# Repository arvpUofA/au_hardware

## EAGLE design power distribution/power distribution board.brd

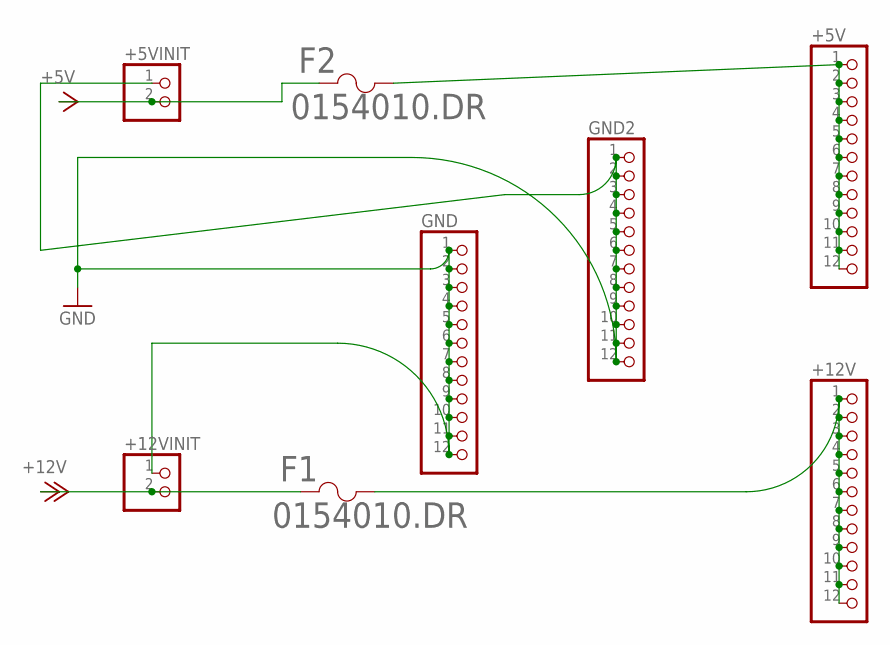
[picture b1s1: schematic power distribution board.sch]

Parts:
+5V, +12V: TERM_BLOCK_12
+5VINIT, +12VINIT: TERM_BLOCK_2TERM_BLOCK_2; 1X02
F1, F2: 0154010.DR; 0154SERIES
GND, GND2: TERM_BLOCK_12

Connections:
+5V: +5VINIT.2, F2.1
+5VDIST: +5V.1, +5V.2, +5V.3, +5V.4, +5V.5, +5V.6, +5V.7, +5V.8, +5V.9, +5V.10, +5V.11, +5V.12, F2.2
+12V: +12VINIT.2, F1.1
+12VDIST: +12V.1, +12V.2, +12V.3, +12V.4, +12V.5, +12V.6, +12V.7, +12V.8, +12V.9, +12V.10, +12V.11, +12V.12, F1.2
GND: +5VINIT.1, +12VINIT.1, GND.1, GND.2, GND.3, GND.4, GND.5, GND.6, GND.7, GND.8, GND.9, GND.10, GND.11, GND.12, GND2.1, GND2.2, GND2.3, GND2.4, GND2.5, GND2.6, GND2.7, GND2.8, GND2.9, GND2.10, GND2.11, GND2.12

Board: 2 copper layers, 8 parts (0 on the bottom side), 5 nets, no tracks yet.

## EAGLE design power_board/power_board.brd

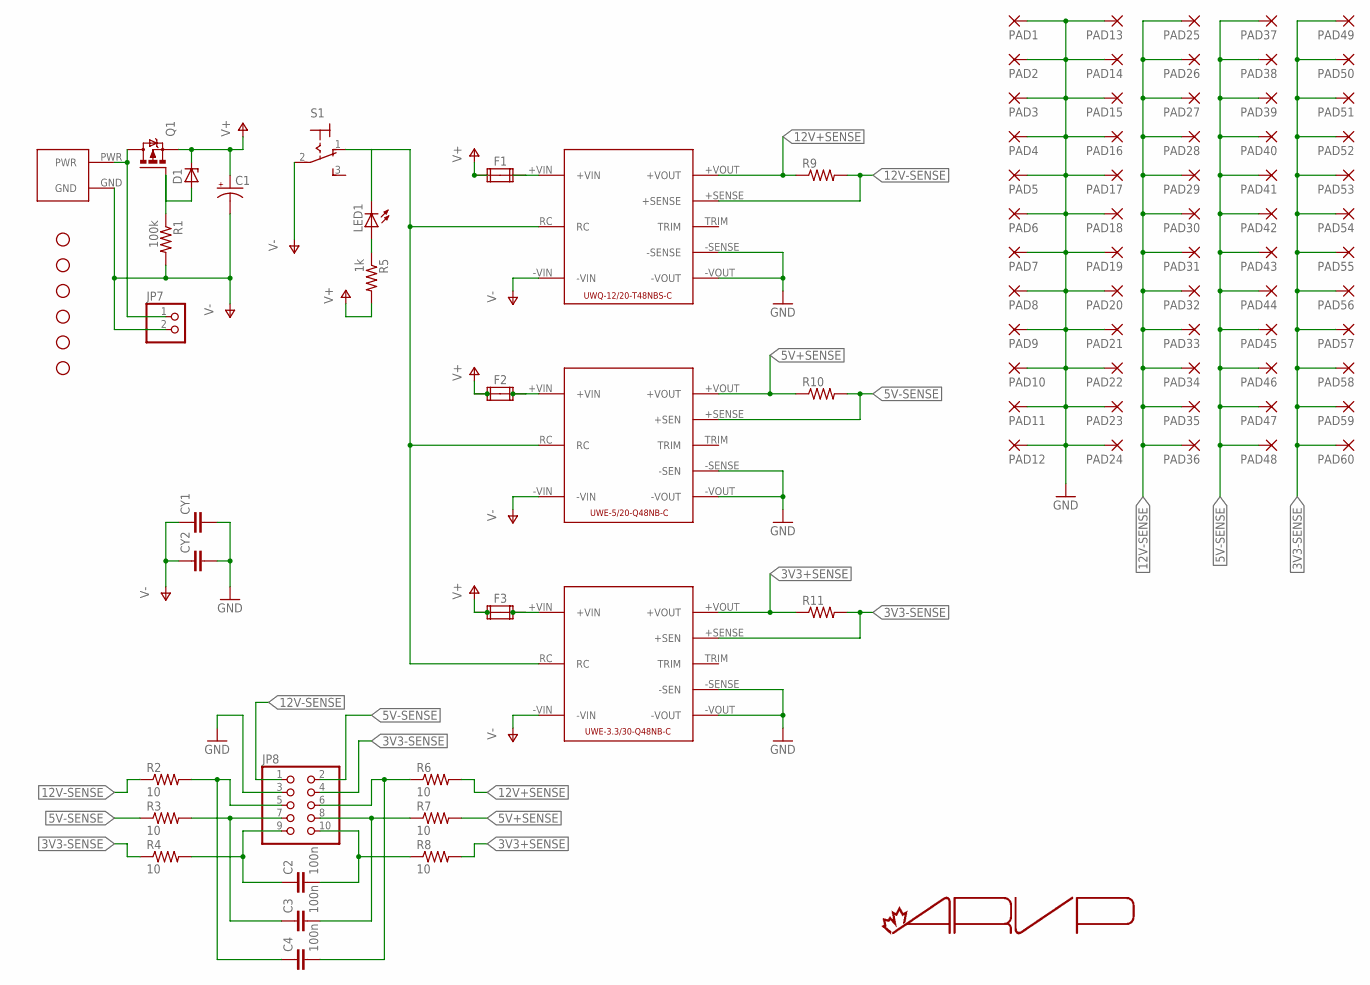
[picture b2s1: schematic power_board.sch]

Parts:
C1: CPOL-USE5-10.5; E5-10,5
C2, C3, C4: 100n; C025-024X044
CY1, CY2: CYYC7B5; YC7B5
D1: ZENER-DIODEDO35Z10; DO35Z10
F1, F2, F3: FUSE2P; FUSE1
JP1, JP2, JP3, JP4, JP5, JP6: STAND-OFF
JP7: PINHD-1X2; 1X02
JP8: PINHD-2X5; 2X05
LED1: LED3MM
P$1: AND_PWR
PAD1, PAD2, PAD3, PAD4, PAD5, PAD6, PAD7, PAD8, PAD9, PAD10, PAD11, PAD12, PAD13, PAD14, PAD15, PAD16, PAD17, PAD18, PAD19, PAD20, PAD21, PAD22, PAD23, PAD24, PAD25, PAD26, PAD27, PAD28, PAD29, PAD30, PAD31, PAD32, PAD33, PAD34, PAD35, PAD36, PAD37, PAD38, PAD39, PAD40, PAD41, PAD42, PAD43, PAD44, PAD45, PAD46, PAD47, PAD48, PAD49, PAD50, PAD51, PAD52, PAD53, PAD54, PAD55, PAD56, PAD57, PAD58, PAD59, PAD60: 2,15/1,0
Q1: IPP80P03P4L04AKSA1; TO220BV
R1: 100k; 0204/7
R2, R3, R4, R6, R7, R8: 10; 0204/5
R5: 1k; 0204/7
R9, R10, R11: R-US_0617/22; 0617/22
S1: M9040P
U1: UWQ-12/20-T48NBS-C; UWQ-12/20-T48
U2: UWE-5/20-Q48NB-C; UWE-100-120W
U3: UWE-3.3/30-Q48NB-C; UWE-100-120W

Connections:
3V3+SENSE: R8.2, R11.1, U3.+VOUT
3V3-SENSE: JP8.4, PAD49.1, PAD50.1, PAD51.1, PAD52.1, PAD53.1, PAD54.1, PAD55.1, PAD56.1, PAD57.1, PAD58.1, PAD59.1, PAD60.1, R4.1, R11.2, U3.+SENSE (+SEN)
5V+SENSE: R7.2, R10.1, U2.+VOUT
5V-SENSE: JP8.2, PAD37.1, PAD38.1, PAD39.1, PAD40.1, PAD41.1, PAD42.1, PAD43.1, PAD44.1, PAD45.1, PAD46.1, PAD47.1, PAD48.1, R3.1, R10.2, U2.+SENSE (+SEN)
12V+SENSE: R6.2, R9.1, U1.+VOUT
12V-SENSE: JP8.1, PAD25.1, PAD26.1, PAD27.1, PAD28.1, PAD29.1, PAD30.1, PAD31.1, PAD32.1, PAD33.1, PAD34.1, PAD35.1, PAD36.1, R2.1, R9.2, U1.+SENSE
GND: CY1.2, CY2.2, JP8.3, PAD1.1, PAD2.1, PAD3.1, PAD4.1, PAD5.1, PAD6.1, PAD7.1, PAD8.1, PAD9.1, PAD10.1, PAD11.1, PAD12.1, PAD13.1, PAD14.1, PAD15.1, PAD16.1, PAD17.1, PAD18.1, PAD19.1, PAD20.1, PAD21.1, PAD22.1, PAD23.1, PAD24.1, U1.-SENSE, U1.-VOUT, U2.-SENSE (-SEN), U2.-VOUT, U3.-SENSE (-SEN), U3.-VOUT
J3: C4.1, JP8.5, R2.2
J4: C4.2, JP8.6, R6.1
J5: C3.1, JP8.7, R3.2
J6: C3.2, JP8.8, R7.1
J7: C2.1, JP8.9, R4.2
J8: C2.2, JP8.10, R8.1
unnamed: LED1.A, R5.1
unnamed: D1.A, Q1.G, R1.1
unnamed: F1.2A, F1.2B, U1.+VIN
unnamed: F2.2A, F2.2B, U2.+VIN
unnamed: F3.2A, F3.2B, U3.+VIN
ON/OFF: LED1.K (C), S1.1 (O), U1.RC, U2.RC, U3.RC
V+: C1.+, D1.C, F1.1A, F1.1B, F2.1A, F2.1B, F3.1A, F3.1B, Q1.S, R5.2
V-: C1.-, CY1.1, CY2.1, JP7.2, P$1.GND, R1.2, S1.2, U1.-VIN, U2.-VIN, U3.-VIN
VBAT+: JP7.1, P$1.PWR, Q1.D

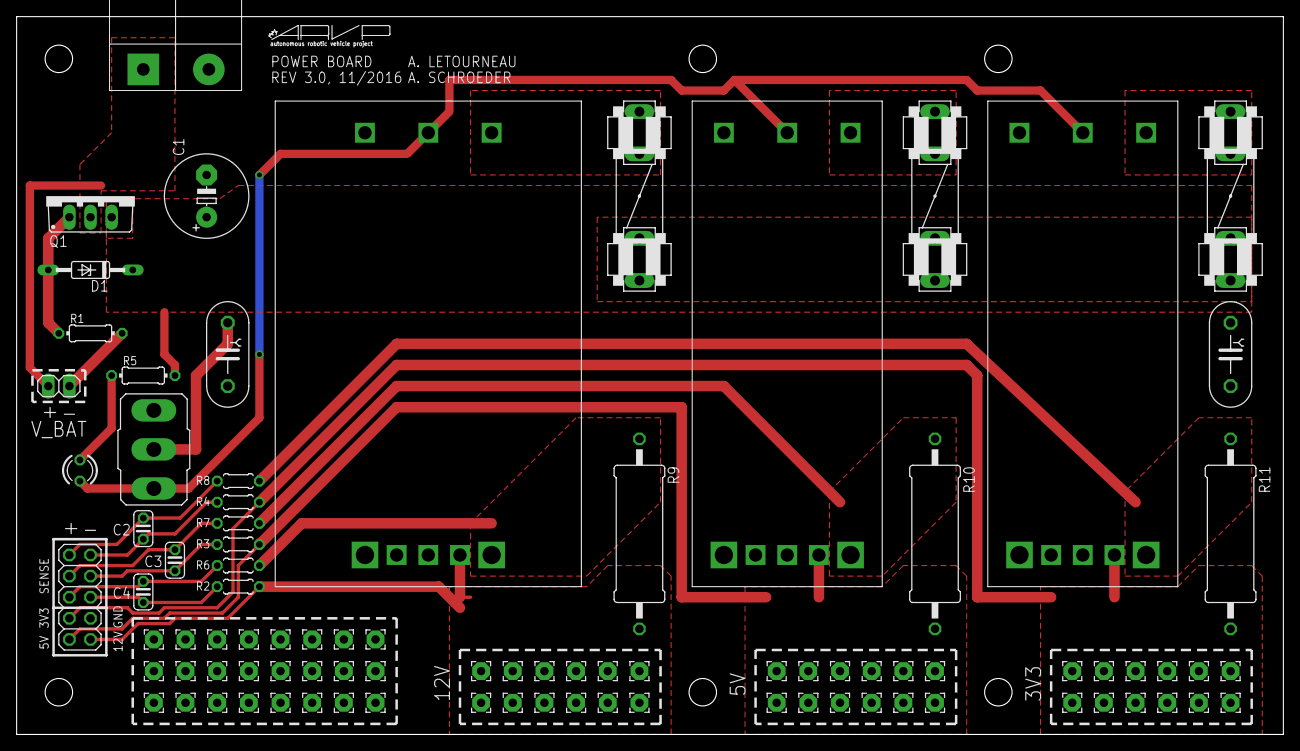
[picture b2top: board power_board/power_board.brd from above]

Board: 2 copper layers, 152.4 x 86.4 mm, 99 parts (0 on the bottom side), 22 nets.

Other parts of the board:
U$1: DINA5_L
U$2: DOCFIELD
U$3: ARVP

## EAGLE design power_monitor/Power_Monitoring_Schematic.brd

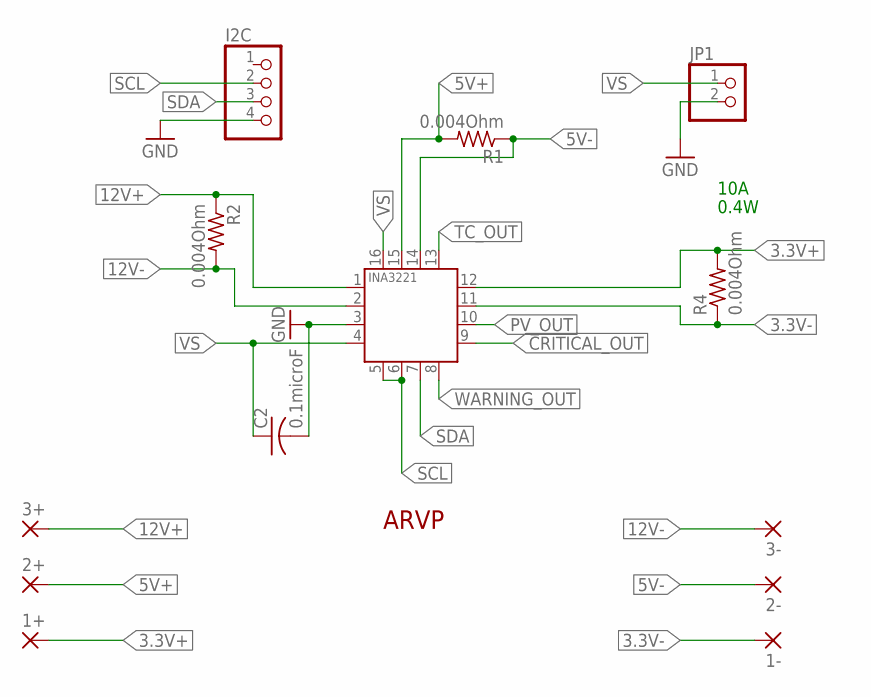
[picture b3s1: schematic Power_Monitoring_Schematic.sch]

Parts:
1+, 1-, 2+, 2-, 3+, 3-: 3,81/1,5A; 3,81/1,5
ARVP1: ARVP_LOGO; ARVP
C2: 0.1microF; C2012
I2C: PINHD-1X4; 1X04
JP1: PINHD-1X2; 1X02
R1, R2, R4: 0.004Ohm; R1206
U1: INA3221.; HVQFN16_4X4

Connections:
3.3V+: 1+.1, R4.2, U1.12 (IN+1)
3.3V-: 1-.1, R4.1, U1.11 (IN-1)
5V+: 2+.1, R1.2, U1.15 (IN+2)
5V-: 2-.1, R1.1, U1.14 (IN-2)
12V+: 3+.1, R2.1, U1.1 (IN-3)
12V-: 3-.1, R2.2, U1.2 (IN+3)
CRITICAL_OUT: U1.9 (CRITICAL)
GND: C2.2, I2C.4, JP1.2, U1.3 (GND)
PV_OUT: U1.10 (PV)
SCL: I2C.2, U1.5 (A0), U1.6 (SCL)
SDA: I2C.3, U1.7 (SDA)
TC_OUT: U1.13 (TC)
VS: C2.1, JP1.1, U1.4 (VS), U1.16 (VPU)
WARNING_OUT: U1.8 (WARNING)

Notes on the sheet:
0.4W
10A

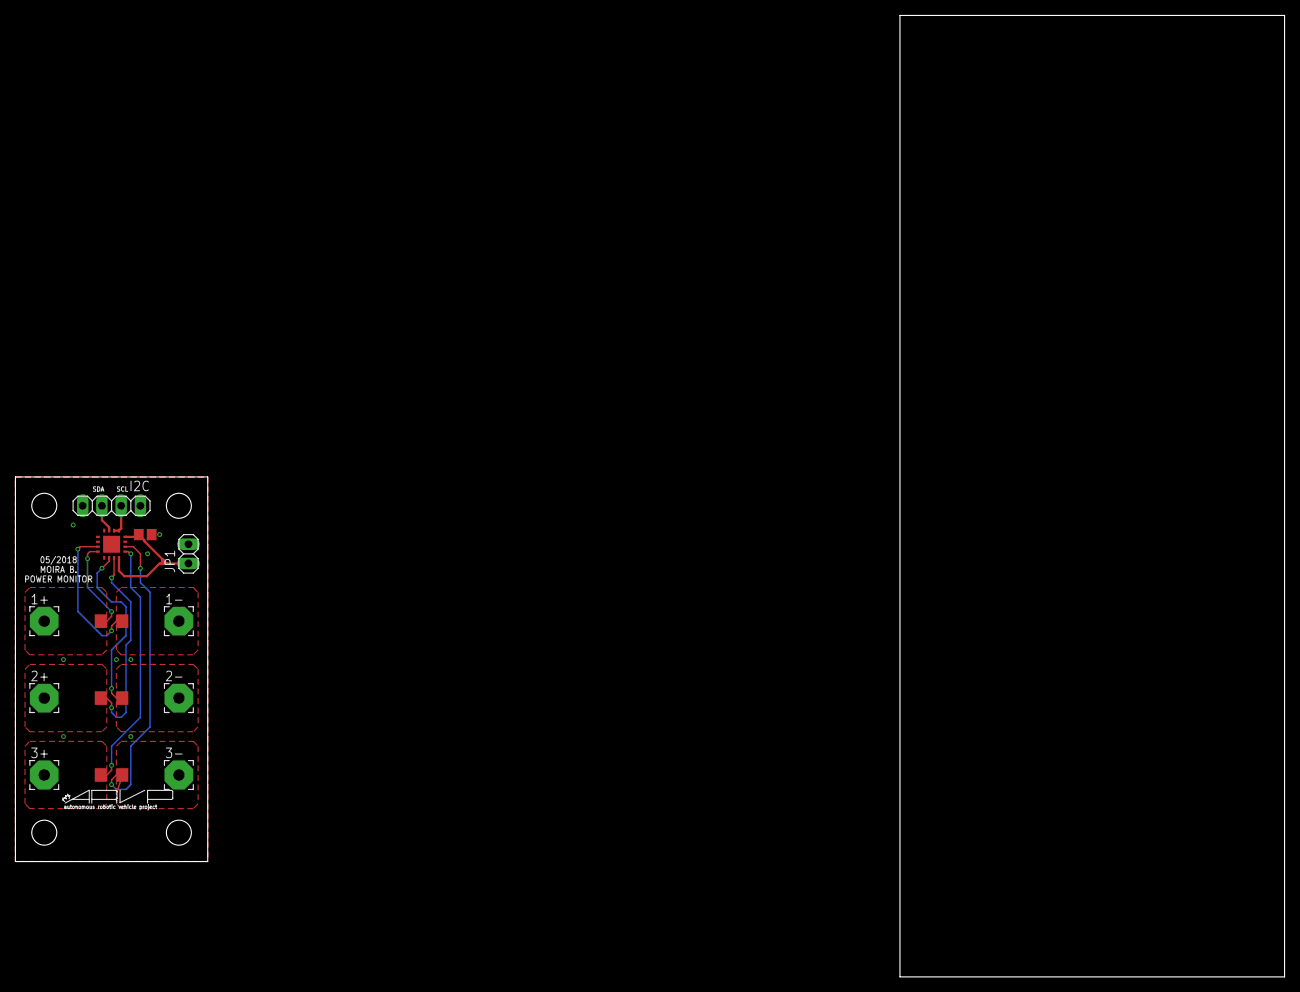
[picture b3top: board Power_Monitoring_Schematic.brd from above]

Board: 2 copper layers, 25.4 x 50.8 mm, 18 parts (0 on the bottom side), 10 nets.

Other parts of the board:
U$1, U$2, U$3, U$4: STAND-OFF

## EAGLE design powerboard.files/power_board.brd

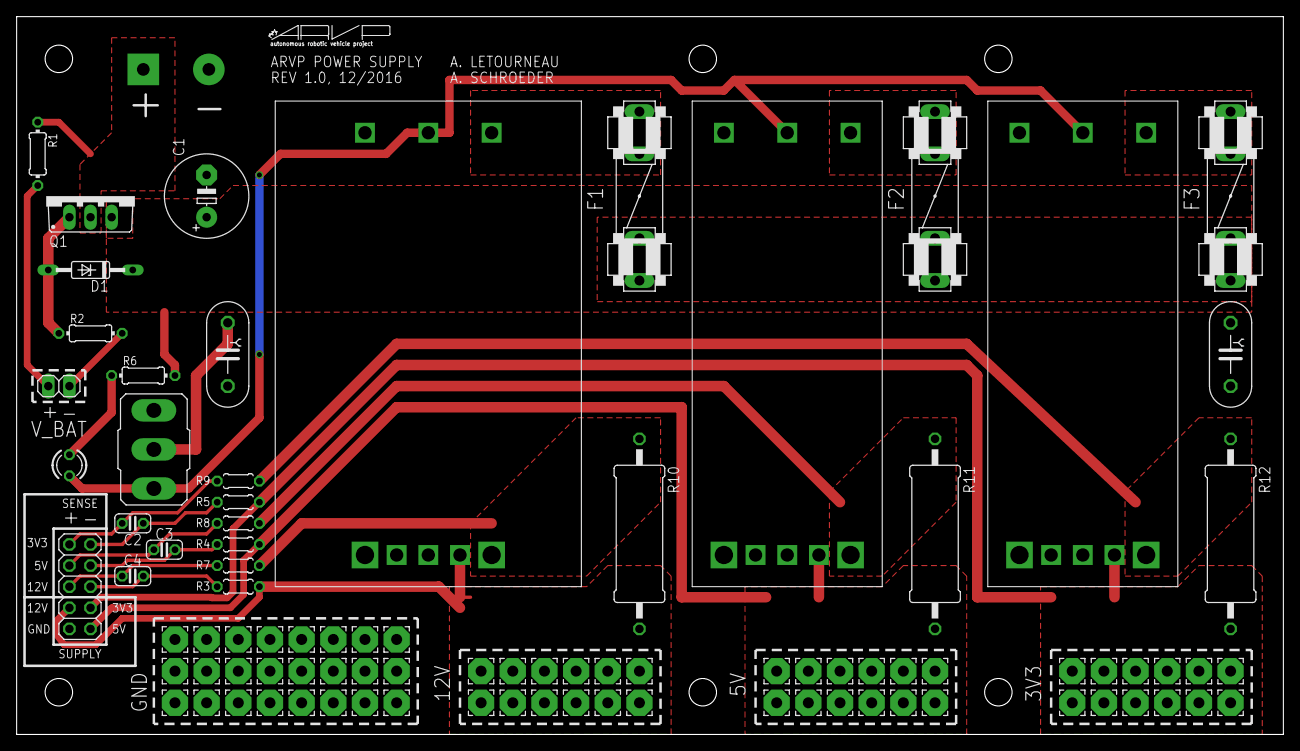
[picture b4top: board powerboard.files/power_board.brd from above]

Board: 2 copper layers, 152.4 x 86.4 mm, 100 parts (0 on the bottom side), 23 nets.

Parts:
C1: E5-10,5
C2, C3, C4: 100n; C025-024X044
CY1, CY2: YC7B5
D1: DO35Z10
F1, F2, F3: FUSE1
JP1, JP2, JP3, JP4, JP5, JP6: STAND-OFF
JP7: 1X02
JP8: 2X05
LED1: LED3MM
P$1: AND_PWR
PAD1, PAD2, PAD3, PAD4, PAD5, PAD6, PAD7, PAD8, PAD9, PAD10, PAD11, PAD12, PAD13, PAD14, PAD15, PAD16, PAD17, PAD18, PAD19, PAD20, PAD21, PAD22, PAD23, PAD24, PAD25, PAD26, PAD27, PAD28, PAD29, PAD30, PAD31, PAD32, PAD33, PAD34, PAD35, PAD36, PAD37, PAD38, PAD39, PAD40, PAD41, PAD42, PAD43, PAD44, PAD45, PAD46, PAD47, PAD48, PAD49, PAD50, PAD51, PAD52, PAD53, PAD54, PAD55, PAD56, PAD57, PAD58, PAD59, PAD60: WIREPAD3,17/1,3; 3,17/1,3
Q1: IPP80P03P4L04AKSA1; TO220BV
R1, R6: 1k; 0204/7
R2: 100k; 0204/7
R3, R4, R5, R7, R8, R9: 10; 0204/5
R10, R11, R12: 0.004; 0617/22
S1: M9040P
U1: UWQ-12/20-T48NBS-C; UWQ-12/20-T48
U2: UWE-5/20-Q48NB-C; UWE-100-120W
U3: UWE-3.3/30-Q48NB-C; UWE-100-120W
U$1: DINA5_L
U$2: DOCFIELD
U$3: ARVP

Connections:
3V3+SENSE: R9.2, R12.1, U3.+VOUT
3V3-SENSE: JP8.3, PAD49.1, PAD50.1, PAD51.1, PAD52.1, PAD53.1, PAD54.1, PAD55.1, PAD56.1, PAD57.1, PAD58.1, PAD59.1, PAD60.1, R5.1, R12.2, U3.+SENSE
5V+SENSE: R8.2, R11.1, U2.+VOUT
5V-SENSE: JP8.1, PAD37.1, PAD38.1, PAD39.1, PAD40.1, PAD41.1, PAD42.1, PAD43.1, PAD44.1, PAD45.1, PAD46.1, PAD47.1, PAD48.1, R4.1, R11.2, U2.+SENSE
12V+SENSE: R7.2, R10.1, U1.+VOUT
12V-SENSE: JP8.4, PAD25.1, PAD26.1, PAD27.1, PAD28.1, PAD29.1, PAD30.1, PAD31.1, PAD32.1, PAD33.1, PAD34.1, PAD35.1, PAD36.1, R3.1, R10.2, U1.+SENSE
GND: CY1.2, CY2.2, JP8.2, PAD1.1, PAD2.1, PAD3.1, PAD4.1, PAD5.1, PAD6.1, PAD7.1, PAD8.1, PAD9.1, PAD10.1, PAD11.1, PAD12.1, PAD13.1, PAD14.1, PAD15.1, PAD16.1, PAD17.1, PAD18.1, PAD19.1, PAD20.1, PAD21.1, PAD22.1, PAD23.1, PAD24.1, U1.-SENSE, U1.-VOUT, U2.-SENSE, U2.-VOUT, U3.-SENSE, U3.-VOUT
J3: C4.1, JP8.5, R3.2
J4: C4.2, JP8.6, R7.1
J5: C3.1, JP8.7, R4.2
J6: C3.2, JP8.8, R8.1
J7: C2.1, JP8.9, R5.2
J8: C2.2, JP8.10, R9.1
unnamed: LED1.A, R6.1
unnamed: JP7.1, R1.2
unnamed: D1.A, Q1.G, R2.1
unnamed: F1.2A, F1.2B, U1.+VIN
unnamed: F2.2A, F2.2B, U2.+VIN
unnamed: F3.2A, F3.2B, U3.+VIN
ON/OFF: LED1.K, S1.1, U1.RC, U2.RC, U3.RC
V+: C1.+, D1.C, F1.1A, F1.1B, F2.1A, F2.1B, F3.1A, F3.1B, Q1.S, R6.2
V-: C1.-, CY1.1, CY2.1, JP7.2, P$1.GND, R2.2, S1.2, U1.-VIN, U2.-VIN, U3.-VIN
VBAT+: P$1.PWR, Q1.D, R1.1

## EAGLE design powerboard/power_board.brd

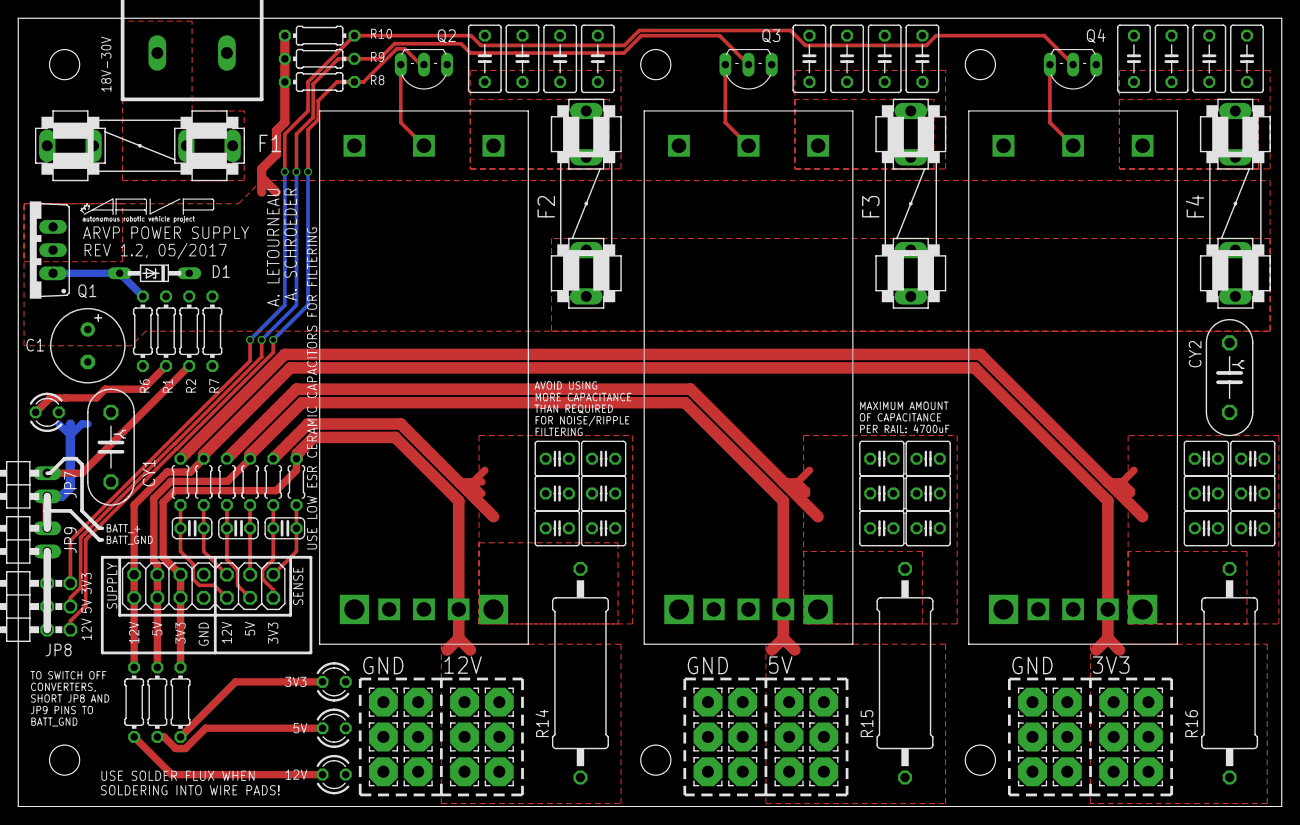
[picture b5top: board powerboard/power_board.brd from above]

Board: 2 copper layers, 138.4 x 86.4 mm, 121 parts (0 on the bottom side), 33 nets.

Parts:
C1: 100u; E3,5-8
C2, C3, C4: 100n; C025-024X044
C5, C6, C7, C8, C9, C10, C11, C12, C13, C14, C15, C16: C050-035X075
C17, C18, C19, C20, C21, C22, C23, C24, C25, C26, C27, C28, C29, C30, C31, C32, C33, C34: C025-040X050
CY1, CY2: YC7B5
D1: BZV10; DO34Z7
F1, F2, F3, F4: FUSE1
JP1, JP2, JP3, JP4, JP5, JP6: STAND-OFF
JP7, JP9: 1X02/90
JP8: 2X03/90
JP10: 2X07
LED1, LED2, LED3, LED4: LED3MM
PAD1, PAD2, PAD3, PAD4, PAD5, PAD6, PAD7, PAD8, PAD9, PAD10, PAD11, PAD12, PAD13, PAD14, PAD15, PAD16, PAD17, PAD18, PAD19, PAD20, PAD21, PAD22, PAD23, PAD24, PAD25, PAD26, PAD27, PAD28, PAD29, PAD30, PAD31, PAD32, PAD33, PAD34, PAD35, PAD36: WIREPAD3,17/1,3; 3,17/1,3
Q1: IPP80P03P4L04AKSA1; TO220BV
Q2, Q3, Q4: 2N4401TFR; TO92-EBC
R1, R17, R18, R19: 36k; 0204/7
R2, R7: 4.7k; 0204/7
R3, R4, R5, R11, R12, R13: 10; 0204/5
R6: 2k; 0204/7
R8, R9, R10: 10k; 0204/7
R14, R15, R16: 0.004; 0617/22
T1: 2_POS_TERMINAL; PHOENIX_CONTACT_MKDS_5/2-7.62
U1: UWE-5/20-Q48NB-C; UWE-100-120W
U2: UWE-3.3/30-Q48NB-C; UWE-100-120W
U4: UWE-12/10-Q48NB-C; UWE-100-120W
U$1: FRAME_A_L
U$2: DOCFIELD
U$3: ARVP

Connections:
3V3+SENSE: C21.1, C22.1, C27.1, C28.1, C33.1, C34.1, R3.1, R16.1, U2.+VOUT
3V3-SENSE: JP10.1, JP10.2, PAD31.1, PAD32.1, PAD33.1, PAD34.1, PAD35.1, PAD36.1, R11.2, R16.2, R19.2, U2.+SENSE
5V+SENSE: C19.1, C20.1, C25.1, C26.1, C31.1, C32.1, R4.1, R15.1, U1.+VOUT
5V-SENSE: JP10.3, JP10.4, PAD25.1, PAD26.1, PAD27.1, PAD28.1, PAD29.1, PAD30.1, R12.2, R15.2, R18.2, U1.+SENSE
12V+SENSE: C17.1, C18.1, C23.1, C24.1, C29.1, C30.1, R5.1, R14.1, U4.+VOUT
12V-SENSE: JP10.5, JP10.6, PAD19.1, PAD20.1, PAD21.1, PAD22.1, PAD23.1, PAD24.1, R13.2, R14.2, R17.2, U4.+SENSE
ENABLE_3V3: Q4.C, U2.RC
ENABLE_5V: Q3.C, U1.RC
ENABLE_12V: Q2.C, U4.RC
GND: C17.2, C18.2, C19.2, C20.2, C21.2, C22.2, C23.2, C24.2, C25.2, C26.2, C27.2, C28.2, C29.2, C30.2, C31.2, C32.2, C33.2, C34.2, CY1.2, CY2.2, JP10.7, JP10.8, LED2.K, LED3.K, LED4.K, PAD1.1, PAD2.1, PAD3.1, PAD4.1, PAD5.1, PAD6.1, PAD7.1, PAD8.1, PAD9.1, PAD10.1, PAD11.1, PAD12.1, PAD13.1, PAD14.1, PAD15.1, PAD16.1, PAD17.1, PAD18.1, U1.-SENSE, U1.-VOUT, U2.-SENSE, U2.-VOUT, U4.-SENSE, U4.-VOUT
J3: C4.1, JP10.9, R3.2
J4: C4.2, JP10.10, R11.1
J5: C3.1, JP10.11, R4.2
J6: C3.2, JP10.12, R12.1
J7: C2.1, JP10.13, R5.2
J8: C2.2, JP10.14, R13.1
unnamed: LED1.A, R1.1
unnamed: JP7.2, R2.2
unnamed: F1.1A, F1.1B, T1.P$1
unnamed: D1.A, Q1.G, R6.1
unnamed: C5.1, C6.1, C11.1, C12.1, F2.2A, F2.2B, U4.+VIN
unnamed: C7.1, C8.1, C13.1, C14.1, F3.2A, F3.2B, U1.+VIN
unnamed: JP8.2, JP8.4, JP8.6, JP9.1
unnamed: LED2.A, R17.1
unnamed: LED3.A, R18.1
unnamed: LED4.A, R19.1
unnamed: C9.1, C10.1, C15.1, C16.1, F4.2A, F4.2B, U2.+VIN
ON/OFF_1: JP8.1, Q2.B, R8.2
ON/OFF_2: JP8.3, Q3.B, R9.2
ON/OFF_3: JP8.5, Q4.B, R10.2
V+: C1.+, D1.C, F2.1A, F2.1B, F3.1A, F3.1B, F4.1A, F4.1B, Q1.S, R1.2, R2.1, R7.1, R8.1, R9.1, R10.1
V-: C1.-, C5.2, C6.2, C7.2, C8.2, C9.2, C10.2, C11.2, C12.2, C13.2, C14.2, C15.2, C16.2, CY1.1, CY2.1, JP7.1, JP9.2, LED1.K, Q2.E, Q3.E, Q4.E, R6.2, R7.2, T1.P$2, U1.-VIN, U2.-VIN, U4.-VIN
VBAT+: F1.2A, F1.2B, Q1.D

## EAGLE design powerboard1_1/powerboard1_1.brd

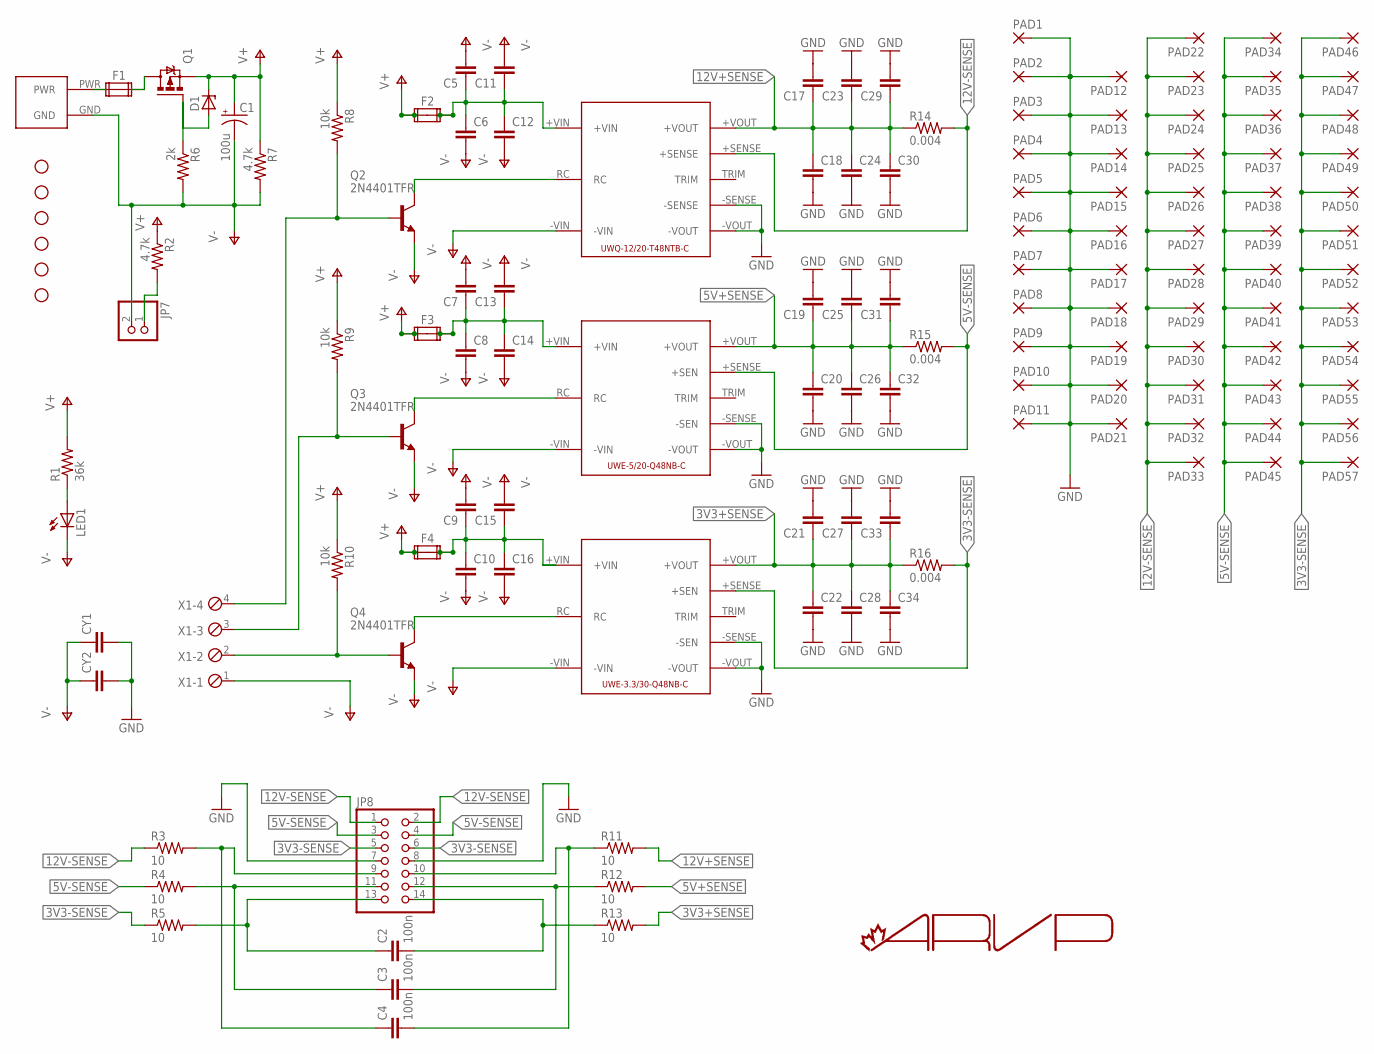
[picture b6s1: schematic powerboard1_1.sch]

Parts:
C1: 100u; E3,5-8
C2, C3, C4: 100n; C025-024X044
C5, C6, C7, C8, C9, C10, C11, C12, C13, C14, C15, C16: C-EU050-035X075; C050-035X075
C17, C18, C19, C20, C21, C22, C23, C24, C25, C26, C27, C28, C29, C30, C31, C32, C33, C34: C-EU025-040X050; C025-040X050
CY1, CY2: CYYC7B5; YC7B5
D1: BZV10; DO34Z7
F1, F2, F3, F4: FUSE2P; FUSE1
JP1, JP2, JP3, JP4, JP5, JP6: STAND-OFF
JP7: PINHD-1X2; 1X02
JP8: PINHD-2X7; 2X07
LED1: LED3MM
P$1: AND_PWR
PAD1, PAD2, PAD3, PAD4, PAD5, PAD6, PAD7, PAD8, PAD9, PAD10, PAD11, PAD12, PAD13, PAD14, PAD15, PAD16, PAD17, PAD18, PAD19, PAD20, PAD21, PAD22, PAD23, PAD24, PAD25, PAD26, PAD27, PAD28, PAD29, PAD30, PAD31, PAD32, PAD33, PAD34, PAD35, PAD36, PAD37, PAD38, PAD39, PAD40, PAD41, PAD42, PAD43, PAD44, PAD45, PAD46, PAD47, PAD48, PAD49, PAD50, PAD51, PAD52, PAD53, PAD54, PAD55, PAD56, PAD57: WIREPAD3,17/1,3; 3,17/1,3
Q1: IPP80P03P4L04AKSA1; TO220BV
Q2, Q3, Q4: 2N4401TFR; TO92-EBC
R1: 36k; 0204/7
R2, R7: 4.7k; 0204/7
R3, R4, R5, R11, R12, R13: 10; 0204/5
R6: 2k; 0204/7
R8, R9, R10: 10k; 0204/7
R14, R15, R16: 0.004; 0617/22
U1: UWQ-12/20-T48NTB-C; UWQ-12/20-T48
U2: UWE-5/20-Q48NB-C; UWE-100-120W
U3: UWE-3.3/30-Q48NB-C; UWE-100-120W
X1: MPT4; 4POL254

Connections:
3V3+SENSE: C21.1, C22.1, C27.1, C28.1, C33.1, C34.1, R13.2, R16.1, U3.+VOUT
3V3-SENSE: JP8.5, JP8.6, PAD46.1, PAD47.1, PAD48.1, PAD49.1, PAD50.1, PAD51.1, PAD52.1, PAD53.1, PAD54.1, PAD55.1, PAD56.1, PAD57.1, R5.1, R16.2, U3.+SENSE (+SEN)
5V+SENSE: C19.1, C20.1, C25.1, C26.1, C31.1, C32.1, R12.2, R15.1, U2.+VOUT
5V-SENSE: JP8.3, JP8.4, PAD34.1, PAD35.1, PAD36.1, PAD37.1, PAD38.1, PAD39.1, PAD40.1, PAD41.1, PAD42.1, PAD43.1, PAD44.1, PAD45.1, R4.1, R15.2, U2.+SENSE (+SEN)
12V+SENSE: C17.1, C18.1, C23.1, C24.1, C29.1, C30.1, R11.2, R14.1, U1.+VOUT
12V-SENSE: JP8.1, JP8.2, PAD22.1, PAD23.1, PAD24.1, PAD25.1, PAD26.1, PAD27.1, PAD28.1, PAD29.1, PAD30.1, PAD31.1, PAD32.1, PAD33.1, R3.1, R14.2, U1.+SENSE
GND: C17.2, C18.2, C19.2, C20.2, C21.2, C22.2, C23.2, C24.2, C25.2, C26.2, C27.2, C28.2, C29.2, C30.2, C31.2, C32.2, C33.2, C34.2, CY1.2, CY2.2, JP8.7, JP8.8, PAD1.1, PAD2.1, PAD3.1, PAD4.1, PAD5.1, PAD6.1, PAD7.1, PAD8.1, PAD9.1, PAD10.1, PAD11.1, PAD12.1, PAD13.1, PAD14.1, PAD15.1, PAD16.1, PAD17.1, PAD18.1, PAD19.1, PAD20.1, PAD21.1, U1.-SENSE, U1.-VOUT, U2.-SENSE (-SEN), U2.-VOUT, U3.-SENSE (-SEN), U3.-VOUT
J3: C4.1, JP8.9, R3.2
J4: C4.2, JP8.10, R11.1
J5: C3.1, JP8.11, R4.2
J6: C3.2, JP8.12, R12.1
J7: C2.1, JP8.13, R5.2
J8: C2.2, JP8.14, R13.1
unnamed: LED1.A, R1.1
unnamed: JP7.1, R2.2
unnamed: F1.1A, F1.1B, P$1.PWR
unnamed: D1.A, Q1.G, R6.1
unnamed: C5.1, C6.1, C11.1, C12.1, F2.2A, F2.2B, U1.+VIN
unnamed: C7.1, C8.1, C13.1, C14.1, F3.2A, F3.2B, U2.+VIN
unnamed: Q2.C, U1.RC
unnamed: Q3.C, U2.RC
unnamed: Q4.C, U3.RC
unnamed: C9.1, C10.1, C15.1, C16.1, F4.2A, F4.2B, U3.+VIN
ON/OFF_1: Q2.B, R8.2, X1.4
ON/OFF_2: Q3.B, R9.2, X1.3
ON/OFF_3: Q4.B, R10.2, X1.2
V+: C1.+, D1.C, F2.1A, F2.1B, F3.1A, F3.1B, F4.1A, F4.1B, Q1.S, R1.2, R2.1, R7.1, R8.1, R9.1, R10.1
V-: C1.-, C5.2, C6.2, C7.2, C8.2, C9.2, C10.2, C11.2, C12.2, C13.2, C14.2, C15.2, C16.2, CY1.1, CY2.1, JP7.2, LED1.K (C), P$1.GND, Q2.E, Q3.E, Q4.E, R6.2, R7.2, U1.-VIN, U2.-VIN, U3.-VIN, X1.1
VBAT+: F1.2A, F1.2B, Q1.D

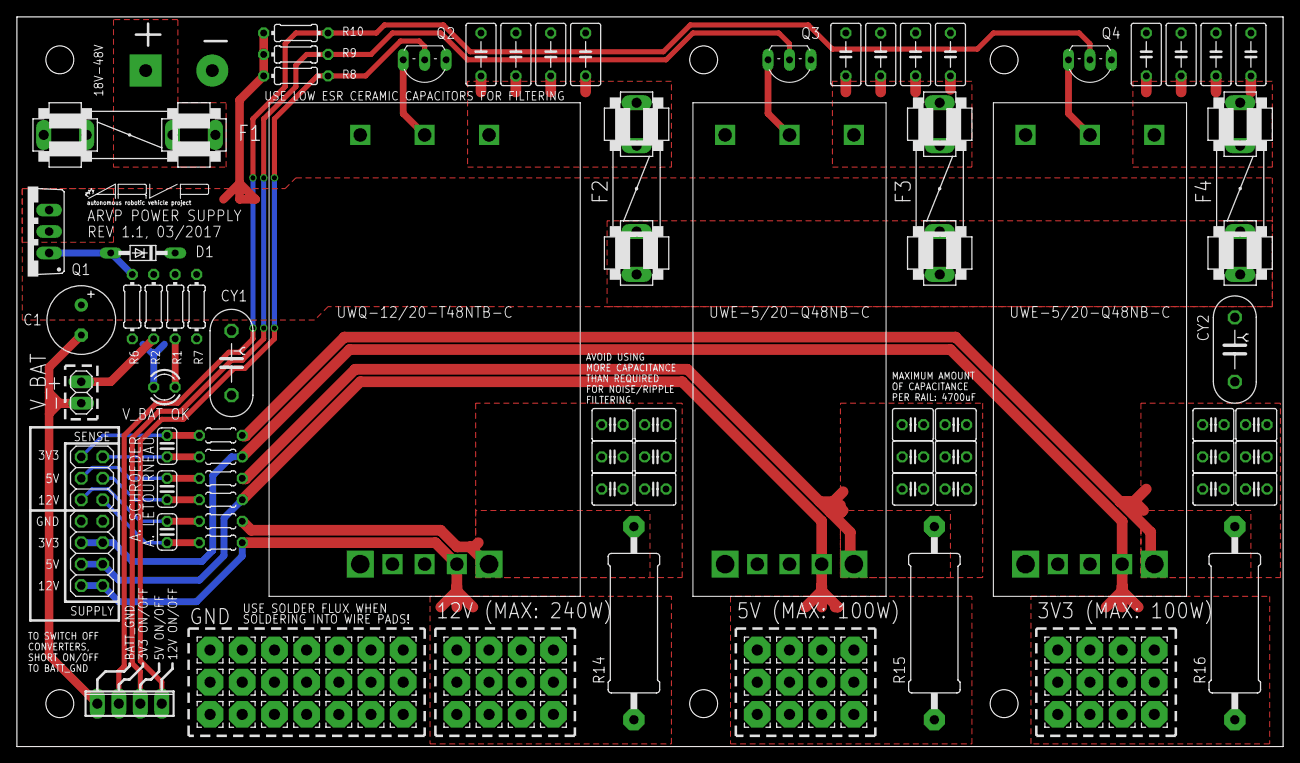
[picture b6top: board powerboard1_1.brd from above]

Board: 2 copper layers, 149.9 x 86.4 mm, 135 parts (0 on the bottom side), 29 nets.

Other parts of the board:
U$1: FRAME_A_L
U$2: DOCFIELD
U$3: ARVP
